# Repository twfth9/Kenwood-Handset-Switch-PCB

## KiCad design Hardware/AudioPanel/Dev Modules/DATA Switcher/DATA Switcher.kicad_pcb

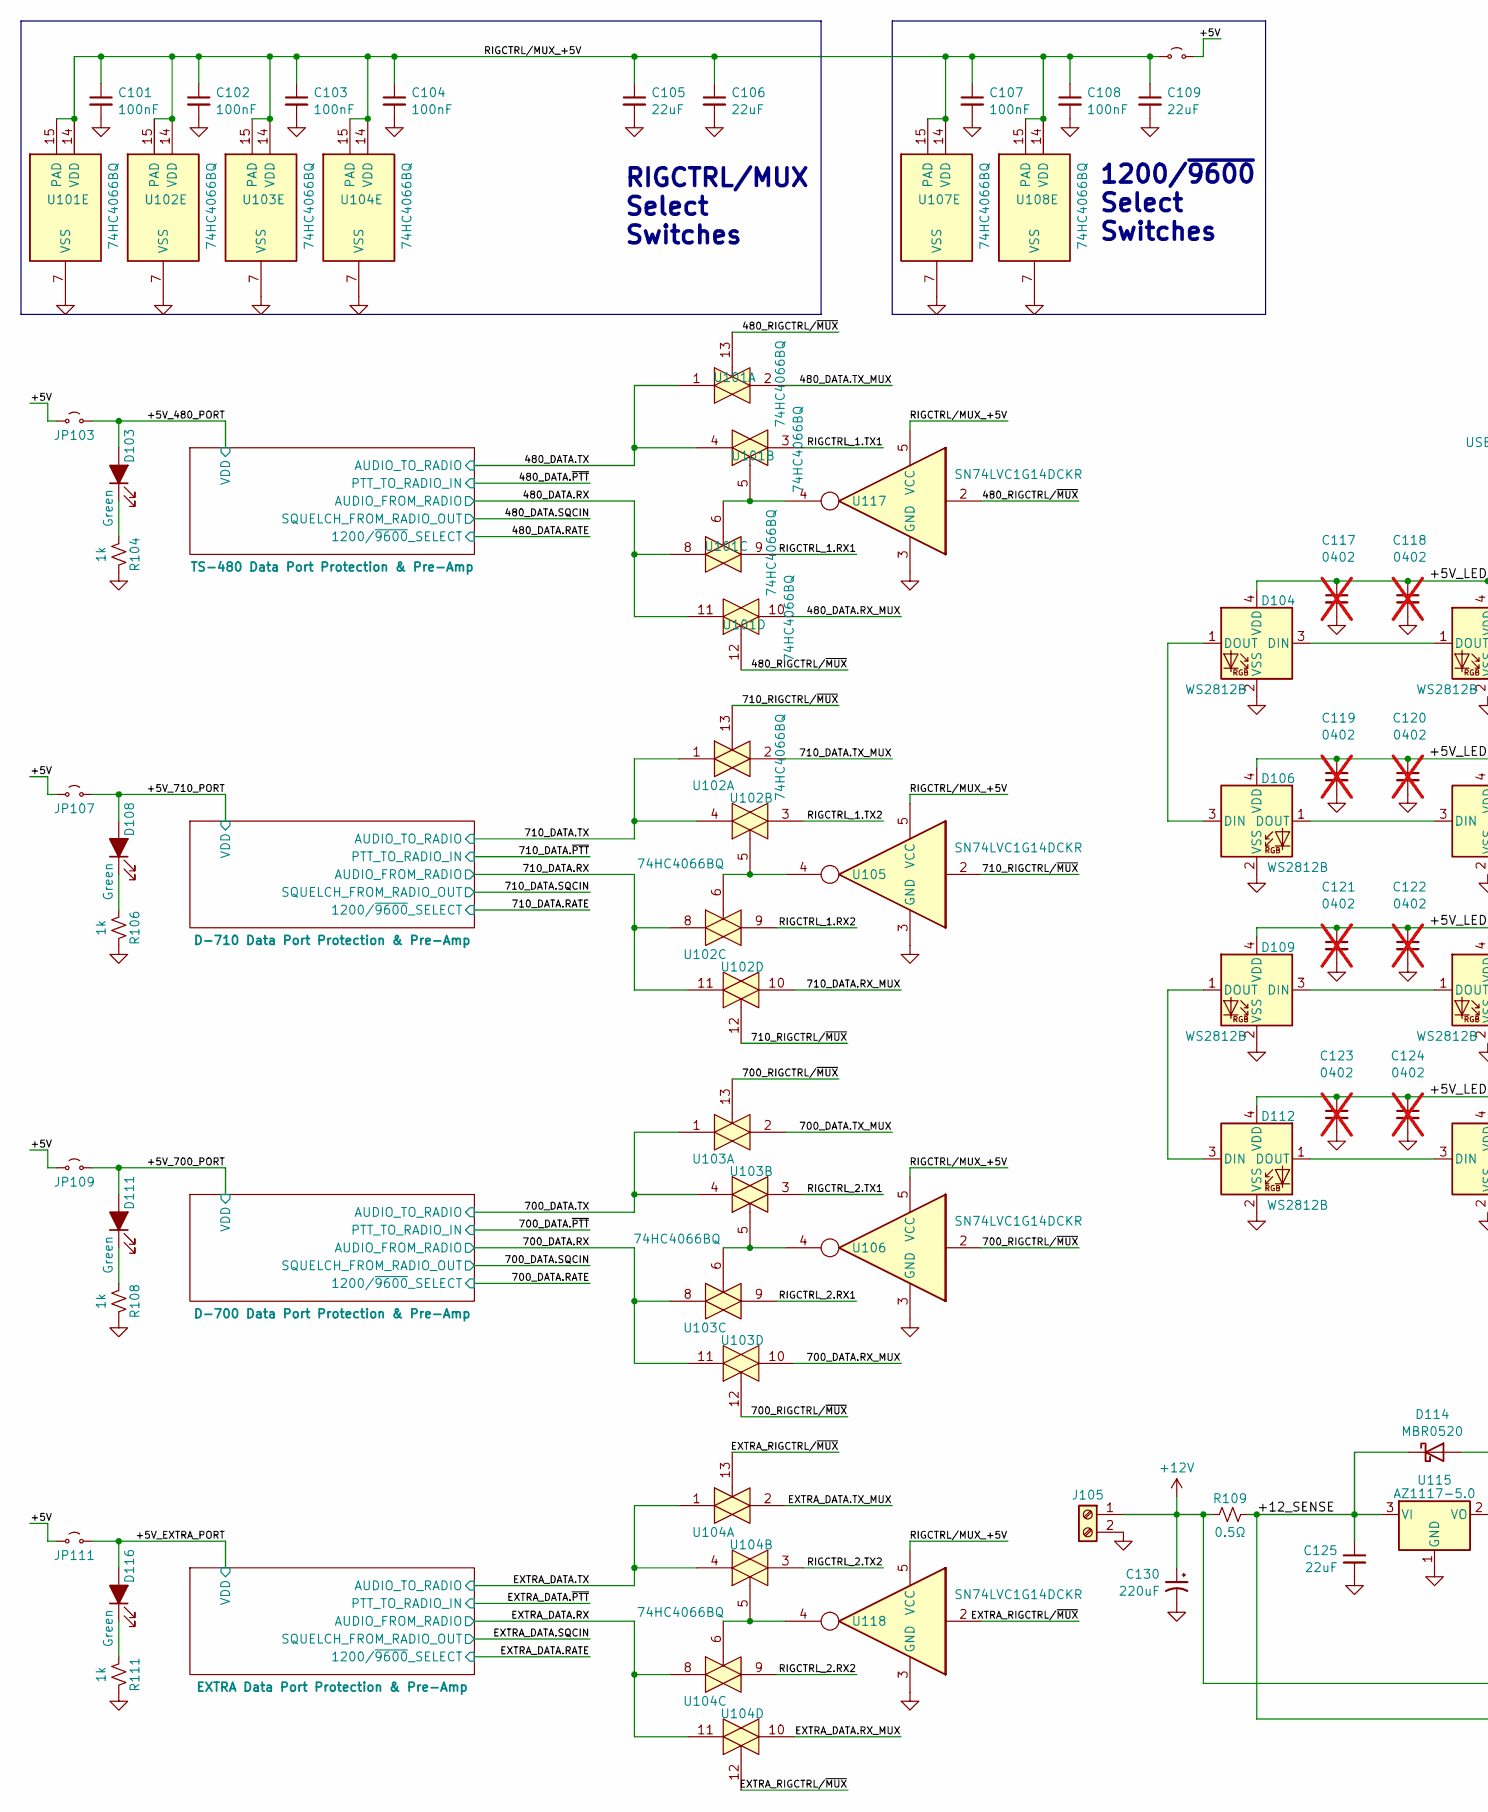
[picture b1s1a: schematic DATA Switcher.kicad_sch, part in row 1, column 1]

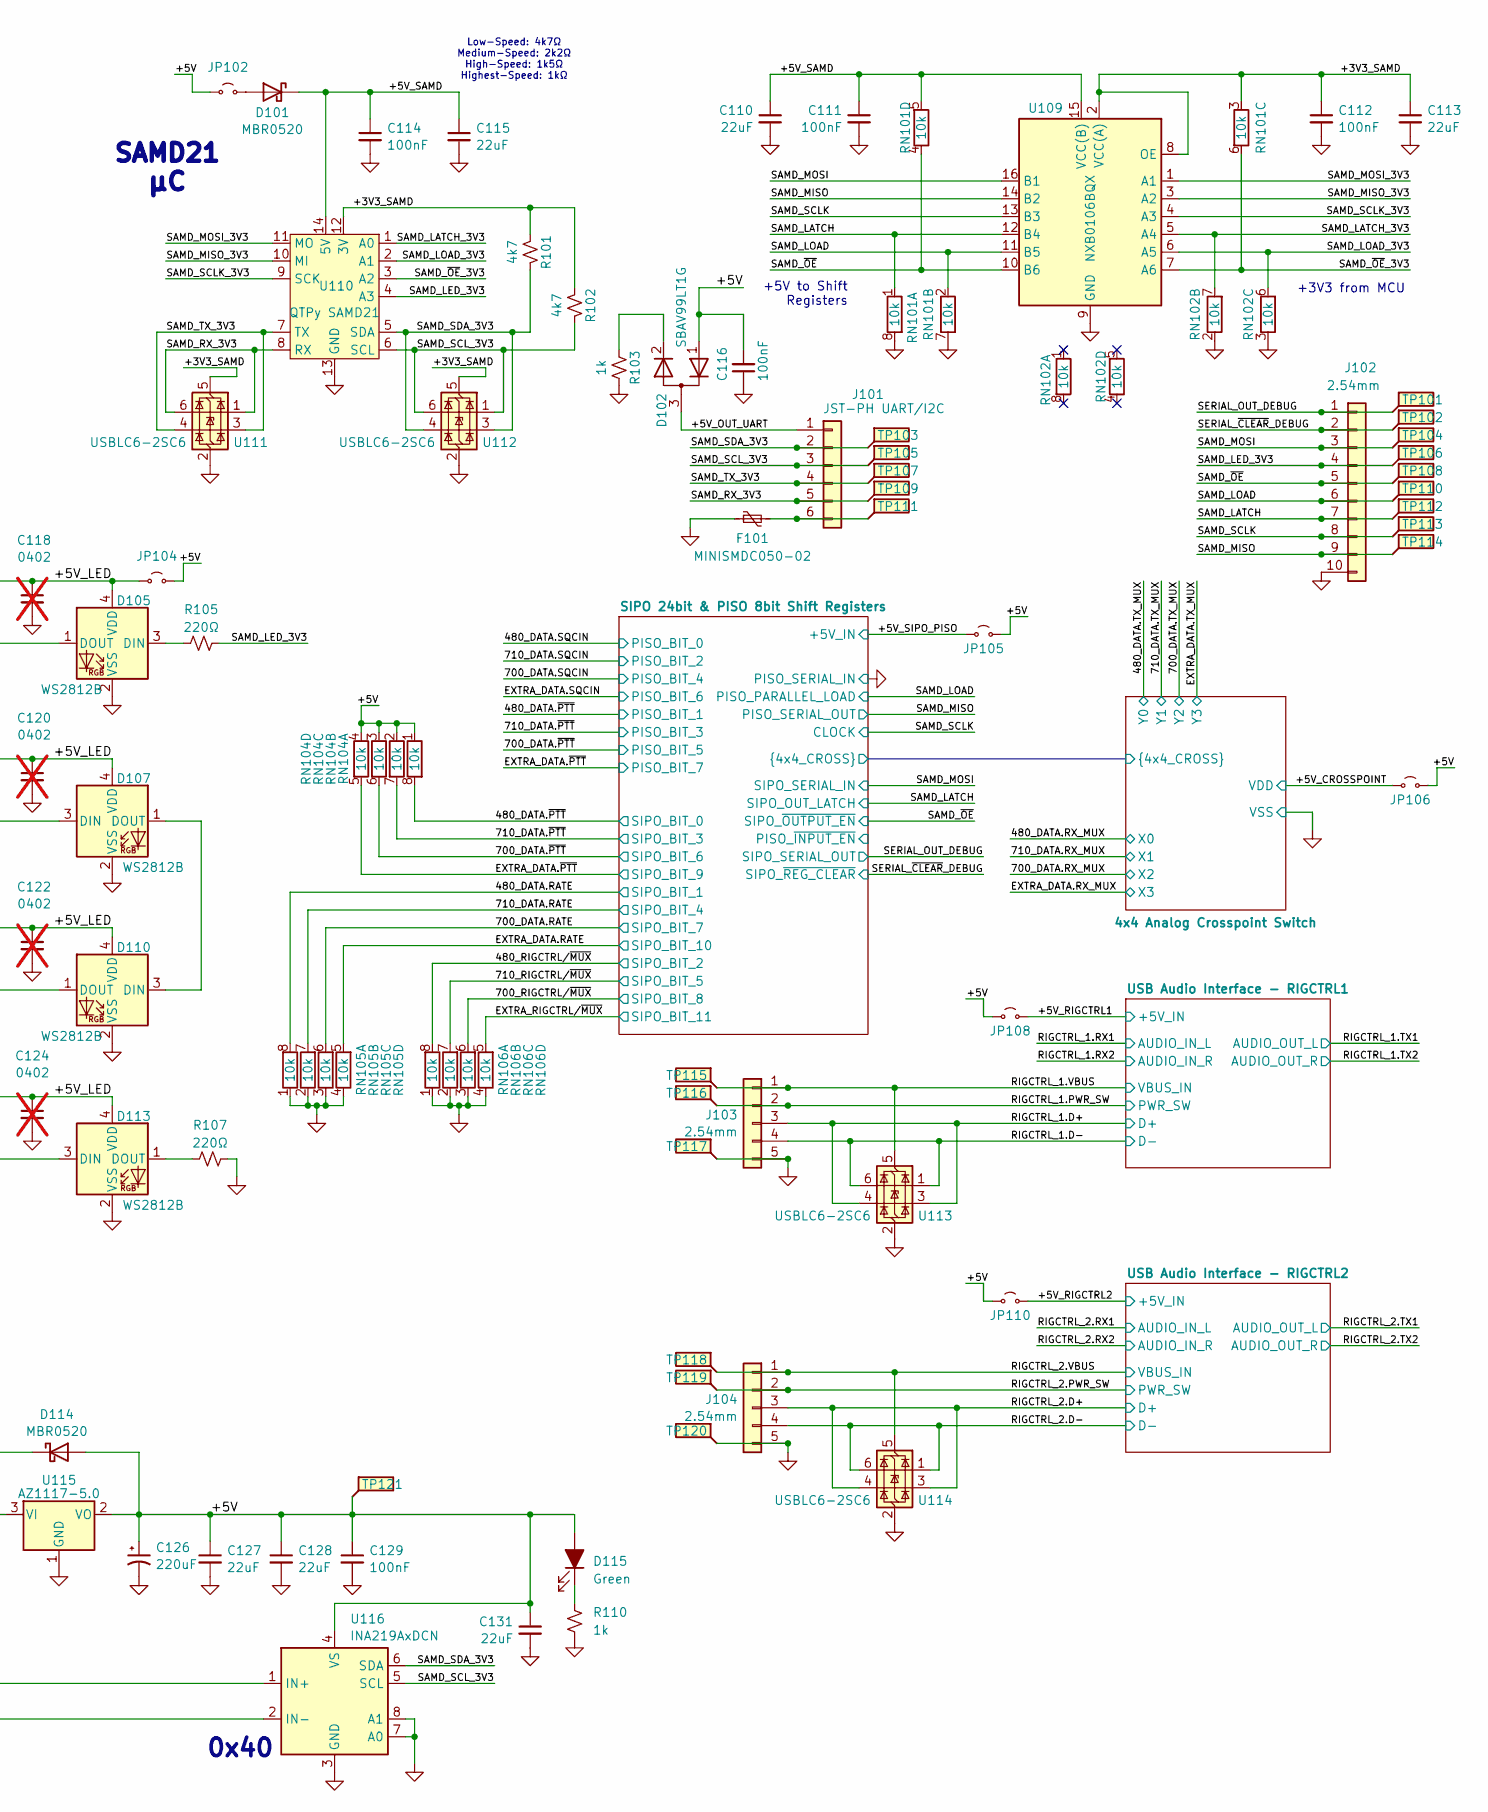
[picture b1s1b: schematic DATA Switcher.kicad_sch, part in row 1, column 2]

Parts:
C101, C102, C103, C104, C107, C108, C111, C112, C114, C116, C129: 100nF; Worthington_C_0402
C105, C106, C109, C110, C113, C115, C125, C127, C128, C131: 22uF; Worthington_C_0603
C117, C118, C119, C120, C121, C122, C123, C124: 0402; Worthington_C_0402; not fitted
C126, C130: 220uF; CP_Elec_6.3x7.7
D101, D114: MBR0520; D_SOD-123
D102: SBAV99LT1G; SOT-23
D103, D108, D111, D116: Green; Worthington_LED_0603; DigiKey Part Number 732-5016-ND
D104, D105, D106, D107, D109, D110, D112, D113: WS2812B; LED_WS2812B-2020_PLCC4_2.0x2.0mm
D115: Green; LED_D5.0mm; DigiKey Part Number 732-5016-ND
F101: MINISMDC050-02; Fuse_0805_2012Metric
J101: JST-PH UART/I2C; PinHeader_1x06_P2.54mm_Vertical
J102: 2.54mm; PinHeader_1x10_P2.54mm_Vertical
J103, J104: 2.54mm; JST_PH_S5B-PH-K_1x05_P2.00mm_Horizontal
J105: Screw_Terminal_01x02; TerminalBlock_Phoenix_MKDS-1,5-2_1x02_P5.00mm_Horizontal
JP101, JP102, JP103, JP104, JP105, JP106, JP107, JP108, JP109, JP110, JP111: Jumper_2_Small_Open; SolderJumper-2_P1.3mm_Open_Pad1.0x1.5mm
R101, R102: 4k7; Worthington_R_0402
R103, R104, R106, R108, R111: 1k; Worthington_R_0402
R105, R107: 220Ω; Worthington_R_0402
R109: 0.5Ω; R_1206_3216Metric
R110: 1k; Worthington_R_0402; DigiKey Part Number 311-510HRCT-ND
RN101, RN102, RN104, RN105, RN106: 10k; RES_ARRAY_4RES_0804
TP101, TP102, TP103, TP104, TP105, TP106, TP107, TP108, TP109, TP110, TP111, TP112, TP113, TP114, TP115, TP116, TP117, TP118, TP119, TP120, TP121: TestPoint_Flag; KEYSTONE_5017
U101, U102, U103, U104, U107, U108: 74HC4066BQ; QFN_104BQX_NEX
U105, U106, U117, U118: SN74LVC1G14DCKR; SOT-353_SC-70-5
U109: NXB0106BQX; RGY16_2P55X2P05
U110: QTPy SAMD21; Py_QT_SAMD21_THT
U111, U112, U113, U114: USBLC6-2SC6; SOT-666
U115: AZ1117-5.0; SOT-223-3_TabPin2
U116: INA219AxDCN; SOT-23-8

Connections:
+12V: C130.1, J105.1, R109.2, U116.1 (IN+)
/480_DATA.RATE: RN105.8; also elsewhere on the board
/480_DATA.RX: U101.8, U101.11; also elsewhere on the board
/480_DATA.RX_MUX: U101.10; also elsewhere on the board
/480_DATA.TX: U101.1, U101.4; also elsewhere on the board
/480_DATA.TX_MUX: U101.2; also elsewhere on the board
/480_DATA.~PTT: RN104.8; also elsewhere on the board
/480_RIGCTRL/~MUX: RN106.8, U101.12, U101.13, U117.2; also elsewhere on the board
/700_DATA.RATE: RN105.6; also elsewhere on the board
/700_DATA.RX: U103.8, U103.11; also elsewhere on the board
/700_DATA.RX_MUX: U103.10; also elsewhere on the board
/700_DATA.TX: U103.1, U103.4; also elsewhere on the board
/700_DATA.TX_MUX: U103.2; also elsewhere on the board
/700_DATA.~PTT: RN104.6; also elsewhere on the board
/700_RIGCTRL/~MUX: RN106.6, U103.12, U103.13, U106.2; also elsewhere on the board
/710_DATA.RATE: RN105.7 (5), U107.5; also elsewhere on the board
/710_DATA.RX: U102.8, U102.11, U107.3, U107.9; also elsewhere on the board
/710_DATA.RX_MUX: U102.10; also elsewhere on the board
/710_DATA.TX: U102.1, U102.4; also elsewhere on the board
/710_DATA.TX_MUX: U102.2; also elsewhere on the board
/710_DATA.~PTT: RN104.7 (5); also elsewhere on the board
/710_RIGCTRL/~MUX: RN106.7 (5), U102.12, U102.13, U105.2; also elsewhere on the board
/+3V3_SAMD: C112.1, C113.1, R101.1, R102.1, RN101.3, U109.2 (VCC(A)), U109.8 (OE), U110.12 (3V), U111.5 (VBUS), U112.5 (VBUS)
/+5V: C116.2, C126.1, C127.1, C128.1, C129.1, C131.1, D102.1 (A), D114.2 (A), D115.2 (A), JP101.2 (B), JP102.2 (B), JP103.2 (B), JP104.1 (A), JP105.2 (B), JP106.2 (B), JP107.2 (B), JP108.2 (B), JP109.2 (B), JP110.2 (B), JP111.2 (B), RN104.1 (4), RN104.2, RN104.3, RN104.4, TP121.1, U115.2 (VO), U116.4 (VS)
/+5V_480_PORT: D103.2 (A), JP103.1 (A); also elsewhere on the board
/+5V_700_PORT: D111.2 (A), JP109.1 (A); also elsewhere on the board
/+5V_710_PORT: D108.2 (A), JP107.1 (A); also elsewhere on the board
/+5V_CROSSPOINT: JP106.1 (A); also elsewhere on the board
/+5V_EXTRA_PORT: D116.2 (A), JP111.1 (A); also elsewhere on the board
/+5V_LED: C117.1, C118.1, C119.1, C120.1, C121.1, C122.1, C123.1, C124.1, D104.4 (VDD), D105.4 (VDD), D106.4 (VDD), D107.4 (VDD), D109.4 (VDD), D110.4 (VDD), D112.4 (VDD), D113.4 (VDD), JP104.2 (B)
/+5V_OUT_UART: D102.3 (common), J101.1
/+5V_RIGCTRL1: JP108.1 (A); also elsewhere on the board
/+5V_RIGCTRL2: JP110.1 (A); also elsewhere on the board
/+5V_SAMD: C110.1, C111.1, C114.1, C115.1, D101.1 (K), RN101.5, U109.15 (VCC(B)), U110.14 (5V)
/+5V_SIPO_PISO: JP105.1 (A); also elsewhere on the board
/+12_SENSE: C125.1, D114.1 (K), R109.1, U115.3 (VI), U116.2 (IN-)
/EXTRA_DATA.RATE: RN105.5, U108.5; also elsewhere on the board
/EXTRA_DATA.RX: U104.8, U104.11, U108.3, U108.9; also elsewhere on the board
/EXTRA_DATA.RX_MUX: U104.10; also elsewhere on the board
/EXTRA_DATA.TX: U104.1, U104.4; also elsewhere on the board
/EXTRA_DATA.TX_MUX: U104.2; also elsewhere on the board
/EXTRA_DATA.~PTT: RN104.5; also elsewhere on the board
/EXTRA_RIGCTRL/~MUX: RN106.5, U104.12, U104.13, U118.2; also elsewhere on the board
/RIGCTRL_1.D+: J103.3, U113.3 (I/O2), U113.4 (I/O2); also elsewhere on the board
/RIGCTRL_1.D-: J103.4, U113.1 (I/O1), U113.6 (I/O1); also elsewhere on the board
/RIGCTRL_1.PWR_SW: J103.2, TP116.1; also elsewhere on the board
/RIGCTRL_1.RX1: U101.9; also elsewhere on the board
/RIGCTRL_1.RX2: U102.9; also elsewhere on the board
/RIGCTRL_1.TX1: U101.3; also elsewhere on the board
/RIGCTRL_1.TX2: U102.3; also elsewhere on the board
/RIGCTRL_1.VBUS: J103.1, TP115.1, U113.5 (VBUS); also elsewhere on the board
/RIGCTRL_2.D+: J104.3, U114.3 (I/O2), U114.4 (I/O2); also elsewhere on the board
/RIGCTRL_2.D-: J104.4, U114.1 (I/O1), U114.6 (I/O1); also elsewhere on the board
/RIGCTRL_2.PWR_SW: J104.2, TP119.1; also elsewhere on the board
/RIGCTRL_2.RX1: U103.9; also elsewhere on the board
/RIGCTRL_2.RX2: U104.9; also elsewhere on the board
/RIGCTRL_2.TX1: U103.3; also elsewhere on the board
/RIGCTRL_2.TX2: U104.3; also elsewhere on the board
/RIGCTRL_2.VBUS: J104.1, TP118.1, U114.5 (VBUS); also elsewhere on the board
/RIGCTRL/MUX_+5V: C101.1, C102.1, C103.1, C104.1, C105.1, C106.1, C107.1, C108.1, C109.1, JP101.1 (A), U101.14 (VDD), U101.15 (PAD), U102.14 (VDD), U102.15 (PAD), U103.14 (VDD), U103.15 (PAD), U104.14 (VDD), U104.15 (PAD), U105.5 (VCC), U106.5 (VCC), U107.14 (VDD), U107.15 (PAD), U108.14 (VDD), U108.15 (PAD), U117.5 (VCC), U118.5 (VCC)
/SAMD_LATCH: J102.7, RN101.1 (4), TP112.1, U109.12 (B4); also elsewhere on the board
/SAMD_LATCH_3V3: RN102.7 (5), U109.5 (A4), U110.1 (A0)
/SAMD_LED_3V3: J102.4, R105.2, TP106.1, U110.4 (A3)
/SAMD_LOAD: J102.6, RN101.2, TP110.1, U109.11 (B5); also elsewhere on the board
/SAMD_LOAD_3V3: RN102.6, U109.6 (A5), U110.2 (A1)
/SAMD_MISO: J102.9, TP114.1, U109.14 (B2); also elsewhere on the board
/SAMD_MISO_3V3: U109.3 (A2), U110.10 (MI)
/SAMD_MOSI: J102.3, TP104.1, U109.16 (B1); also elsewhere on the board
/SAMD_MOSI_3V3: U109.1 (A1), U110.11 (MO)
/SAMD_RX_3V3: J101.5, TP109.1, U110.8 (RX), U111.1 (I/O1), U111.6 (I/O1)
/SAMD_SCLK: J102.8, TP113.1, U109.13 (B3); also elsewhere on the board
/SAMD_SCLK_3V3: U109.4 (A3), U110.9 (SCK)
/SAMD_SCL_3V3: J101.3, R102.2, TP105.1, U110.6 (SCL), U112.1 (I/O1), U112.6 (I/O1), U116.5 (SCL)
/SAMD_SDA_3V3: J101.2, R101.2, TP103.1, U110.5 (SDA), U112.3 (I/O2), U112.4 (I/O2), U116.6 (SDA)
/SAMD_TX_3V3: J101.4, TP107.1, U110.7 (TX), U111.3 (I/O2), U111.4 (I/O2)
/SAMD_~OE: J102.5, RN101.4, TP108.1, U109.10 (B6); also elsewhere on the board
/SAMD_~OE_3V3: RN101.6, U109.7 (A6), U110.3 (A2)
/SERIAL_OUT_DEBUG: J102.1, TP101.1; also elsewhere on the board
/SERIAL_~CLEAR_DEBUG: J102.2, TP102.1; also elsewhere on the board
GND: C101.2, C102.2, C103.2, C104.2, C105.2, C106.2, C107.2, C108.2, C109.2, C110.2, C111.2, C112.2, C113.2, C114.2, C115.2, C116.1, C117.2, C118.2, C119.2, C120.2, C121.2, C122.2, C123.2, C124.2, C125.2, C126.2, C127.2, C128.2, C129.2, C130.2, C131.2, D104.2 (VSS), D105.2 (VSS), D106.2 (VSS), D107.2 (VSS), D109.2 (VSS), D110.2 (VSS), D112.2 (VSS), D113.2 (VSS), F101.1, J102.10, J103.5, J104.5, J105.2, R103.1, R104.2, R106.2, R107.2, R108.2, R110.1, R111.2, RN101.7 (5), RN101.8, RN102.2, RN102.3, RN105.1 (4), RN105.2, RN105.3, RN105.4, RN106.1 (4), RN106.2, RN106.3, RN106.4, TP117.1, TP120.1, U101.7 (VSS), U102.7 (VSS), U103.7 (VSS), U104.7 (VSS), U105.3 (GND), U106.3 (GND), U107.7 (VSS), U108.7 (VSS), U109.9 (GND), U109.17 (GND), U110.13 (GND), U111.2 (GND), U112.2 (GND), U113.2 (GND), U114.2 (GND), U115.1 (GND), U116.3 (GND), U116.7 (A0), U116.8 (A1), U117.3 (GND), U118.3 (GND); also elsewhere on the board
unnamed: D101.2 (A), JP102.1 (A)
unnamed: D102.2 (K), R103.2
unnamed: D103.1 (K), R104.1
unnamed: D104.3 (DIN), D105.1 (DOUT)
unnamed: D104.1 (DOUT), D106.3 (DIN)
unnamed: D105.3 (DIN), R105.1
unnamed: D106.1 (DOUT), D107.3 (DIN)
unnamed: D107.1 (DOUT), D110.3 (DIN)
unnamed: D108.1 (K), R106.1
unnamed: D109.3 (DIN), D110.1 (DOUT)
unnamed: D109.1 (DOUT), D112.3 (DIN)
unnamed: D111.1 (K), R108.1
unnamed: D112.1 (DOUT), D113.3 (DIN)
unnamed: D113.1 (DOUT), R107.1
unnamed: D115.1 (K), R110.2
unnamed: D116.1 (K), R111.1
unnamed: F101.2, J101.6, TP111.1
unnamed 294: U107.8; also elsewhere on the board
unnamed 295: U107.4; also elsewhere on the board
unnamed 298: U108.8; also elsewhere on the board
unnamed 299: U108.4; also elsewhere on the board
unnamed: U101.5, U101.6, U117.4
unnamed: U102.5, U102.6, U105.4
unnamed: U103.5, U103.6, U106.4
unnamed: U104.5, U104.6, U118.4
unnamed 320: U107.6; also elsewhere on the board
unnamed 322: U108.6; also elsewhere on the board

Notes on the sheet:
1200/~{9600} Select Switches
SAMD21 µC
+3V3 from MCU
Low-Speed: 4k7Ω Medium-Speed: 2k2Ω High-Speed: 1k5Ω Highest-Speed: 1kΩ
RIGCTRL/MUX Select Switches
+5V to Shift Registers
0x40
